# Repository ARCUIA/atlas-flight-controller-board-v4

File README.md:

# atlas-flight-controller-board-v4
Flight controller for 2026-2027 school year. KiCad v10. STM32F405RG-based board. Switching to SAM-M10Q GPS module.

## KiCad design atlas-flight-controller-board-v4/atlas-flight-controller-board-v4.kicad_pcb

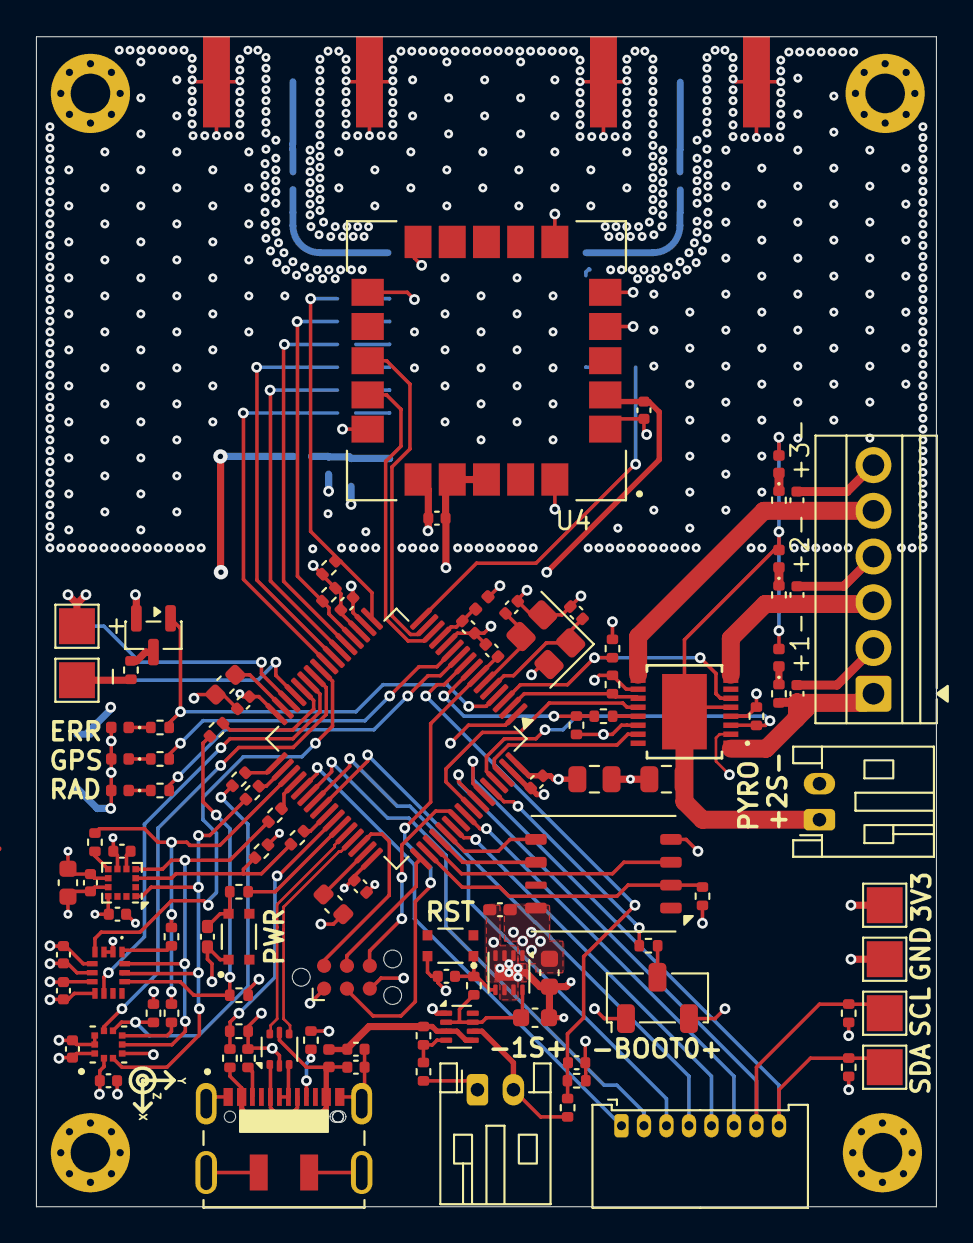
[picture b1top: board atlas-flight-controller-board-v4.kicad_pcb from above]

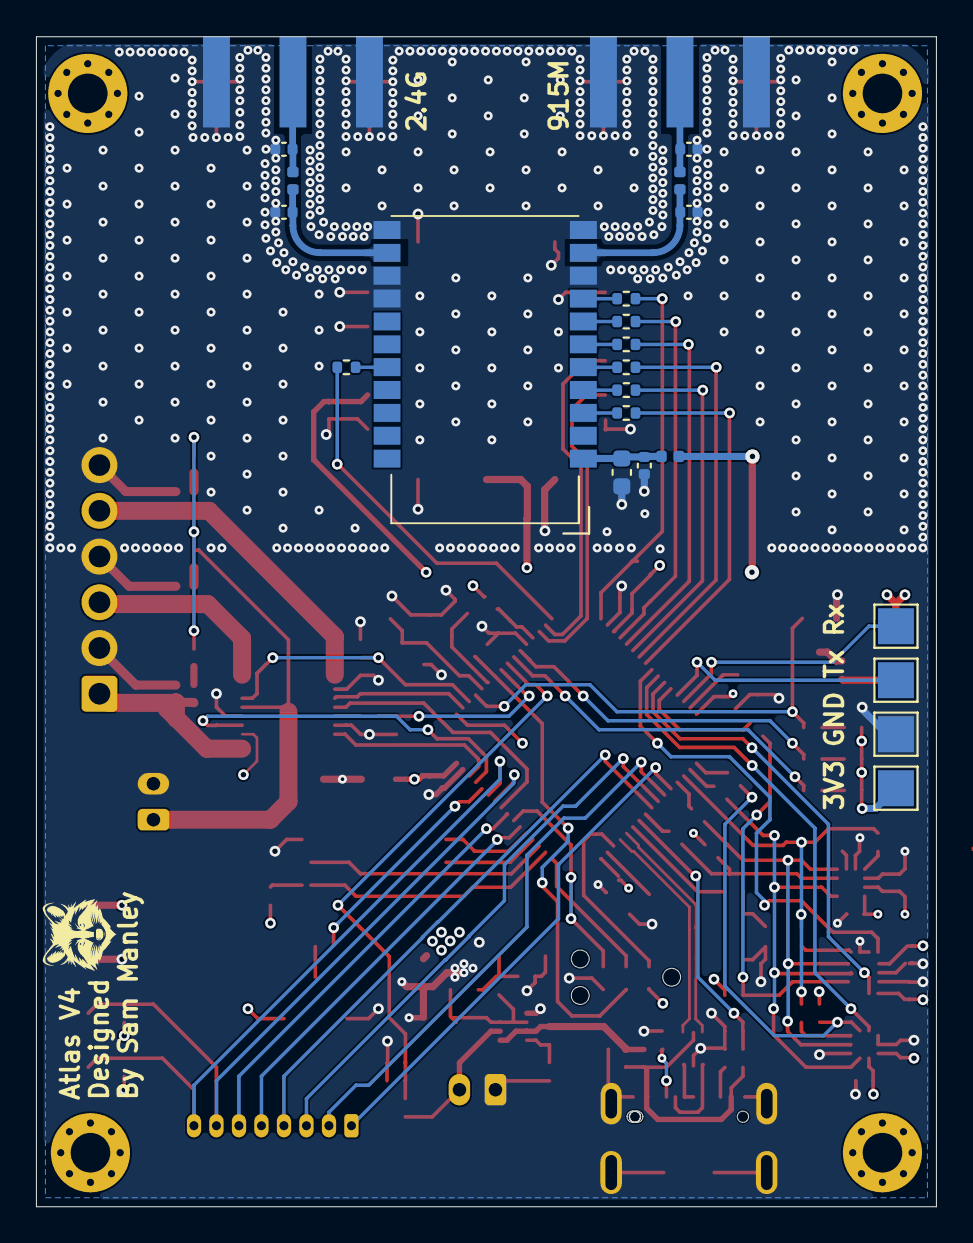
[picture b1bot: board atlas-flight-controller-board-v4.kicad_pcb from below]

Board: 4 copper layers, 50.0 x 65.0 mm, 134 parts (23 on the bottom side), 102 nets.

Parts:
A1: LPS22DFTR; XDCR_LPS22DFTR
C1: 4u7; C_0805_2012Metric
C3, C4, C5, C6, C7, C10, C17, C18, C19, C20, C22, C23, C25, C26, C32, C34, C35, C38, C39: 100n; C_0402_1005Metric
C11, C12: 10p; C_0402_1005Metric
C13, C14: 2u2; C_0603_1608Metric
C15, C16: 100n; C_0402_1005Metric_Pad0.74x0.62mm_HandSolder
C24, C33: 10u; C_0603_1608Metric
C27: 220n; C_0402_1005Metric
C28, C29, C30, C31: C_0402_1005Metric
C36, C37: 1u; C_0603_1608Metric
C40: 10u; C_0805_2012Metric
C41, C42, C43: 10n; C_0402_1005Metric
D1, D2, D3, D5, D6, D7: LED-Red; LED_0402_1005Metric
FB1, FB2, FB3: 120R @ 100 MHz; L_0402_1005Metric
H1, H2, H3, H4: MountingHole; MountingHole_2.2mm_M2_Pad_Via
IC1: LSM6DSV80XTR; LSM6DSV16BXTR
J1: DX07S016JA1R1500; JAE_DX07S016JA1R1500
J2: Conn_01x08; Molex_PicoBlade_53048-0810_1x08_P1.25mm_Horizontal
J3: SWD_TC2030-NL; Tag-Connect_TC2030-IDC-NL_2x03_P1.27mm_Vertical
J4, J5: Conn_Coaxial; SMA_Amphenol_132289_EdgeMount
J6: Batt Conn; JST_PH_S2B-PH-K_1x02_P2.00mm_Horizontal
J7: Conn_01x02; JST_PH_S2B-PH-K_1x02_P2.00mm_Horizontal
J8: Screw_Terminal_01x06; TerminalBlock_Xinya_XY308-2.54-6P_1x06_P2.54mm_Horizontal
L1, L2: L_0402_1005Metric
Q1: BSS138; SOT-23
R1, R10, R18, R21, R42, R43, R44, R45, R46, R47, R48: 10k; R_0402_1005Metric
R2, R20, R22: 33k; R_0402_1005Metric
R3: 82k; R_0402_1005Metric
R4, R5: 5k1; R_0402_1005Metric
R6, R7, R8, R9: 1k5; R_0402_1005Metric
R11, R12, R13, R14, R15, R16, R17: 470; R_0402_1005Metric
R19, R23: 100k; R_0402_1005Metric
R24, R25, R26, R27, R28, R29: 15k; R_0402_1005Metric
R30, R31: 330; R_0402_1005Metric
R34, R35, R36, R37, R38, R39, R40, R41: 33; R_0402_1005Metric
SW1: SW_SPDT; Nidec_Copal_CAS-120A
SW2: SW_Push; SW_USLPT2819DT2TR
SW3: HARD_RESET; SW_USLPT2819DT2TR
TP1, TP2, TP3, TP4, TP5, TP6, TP7, TP8, TP9, TP10: TestPoint_Square; TestPoint_Pad_2.0x2.0mm
U1: USBLC6; SOT-666
U2: STM32F405RGTx; LQFP-64_10x10mm_P0.5mm
U3: LGA-8_8x6.2mm_P1.27mm
U4: SAM-M10Q-00B; XCVR_SAM-M10Q-00B
U6: LIS2MDL; LGA-12_2x2mm_P0.5mm
U7: Value; Wio-LR2021_V1
U8: TPS7A2133PQWDSGRQ1; Texas_DSG0008A_WSON-8-1EP_2x2mm_P0.5mm_EP0.9x1.6mm
U9: TPS2116DRL; SOT-583-8
U13: VNQ7140AJTR; SOIC_0AJTR_STM
Y1: 16 MHz; Crystal_SMD_3225-4Pin_3.2x2.5mm

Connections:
+3.3VA: C7.1, FB1.1, U2.13 (VDDA)
+3V3: A1.1 (VDD_IO), A1.10 (VDD), C1.1, C3.1, C4.1, C5.1, C6.1, C15.1, C17.1, C18.1, C19.1, C20.2, C22.1, C23.1, C24.2, C25.2, C26.2, C36.1, D1.2 (A), D2.2 (A), D3.2 (A), FB1.2, FB2.2, IC1.5 (VDDIO), IC1.8 (VDD), J3.1 (VCC), R18.1, R42.1, R43.1, R44.1, R45.1, R46.1, R47.1, R48.1, SW1.3 (C), TP1.1 (1_1), TP5.1 (1_1), TP7.1 (1_1), U2.1 (VBAT), U2.19 (VDD), U2.32 (VDD), U2.48 (VDD), U2.64 (VDD), U3.8 (VDD), U4.2 (V_IO), U4.17 (VCC), U4.18 (~RESET), U6.9 (VDD), U6.10 (VDD_IO), U8.1 (OUT), U13.2 (SEN)
/power/MUX OUT: C37.1, R21.2, U8.8 (IN), U9.2 (VOUT), U9.7 (VOUT)
/power/VBATT+: J6.2, R22.1, U9.6 (VIN2)
/radio/2G4_RF_ANT: C28.1, J4.1 (In), L1.1
/radio/2G4_RF_MOD: C29.1, L1.2, U7.13 (2.4G_RF)
/radio/915_RF_ANT: C31.1, J5.1 (In), L2.1
/radio/915_RF_MOD: C30.1, L2.2, U7.10 (Sub-G_RF)
/stm32/BOOT0: R1.1, U2.60 (BOOT0)
/stm32/HSE_IN: C11.1, U2.5 (PH0), Y1.1
/stm32/HSE_OUT: C12.1, U2.6 (PH1), Y1.3
/stm32/SW_BOOT0: R1.2, SW1.2 (B)
/stm32/USB_DP+: J1.6 (D+), J1.7 (D+), U1.3 (I/O2), U1.4 (I/O2), U2.45 (PA12)
/stm32/USB_DP-: J1.5 (D-), J1.8 (D-), U1.1 (I/O1), U1.6 (I/O1), U2.44 (PA11)
/stm32/VBUS_SENSE: R2.1, R3.2, U2.42 (PA9)
BARO_INT: A1.7 (INT_DRDY), U2.26 (PB0)
BATT_SENSE: C38.1, R22.2, R23.1, U2.9 (PC1)
BUSY_LORA: R11.2, R18.2, U2.17 (PA3)
CAMERA_POWER_SWITCH: J2.6, U2.56 (PB4)
CS_BARO: A1.6 (CS), R39.1, R44.2
CS_FLASH: R45.2, U2.50 (PA15), U3.2 (CS)
CS_IMU: IC1.12 (CS), R40.1, R43.2
CS_LORA: R12.2, R46.2, U2.20 (PA4)
CS_MAG: R41.1, R42.2, U6.3 (CS)
ERROR_LED: Q1.1 (G), R8.2, U2.4 (PC15)
EXT_RX: TP10.1 (1_1), U2.30 (PB11)
EXT_SCL: J2.7, R47.2, TP3.1 (1_1), U2.58 (PB6)
EXT_SDA: J2.8, R48.2, TP4.1 (1_1), U2.59 (PB7)
EXT_TX: TP9.1 (1_1), U2.29 (PB10)
GND: A1.3 (RES), A1.8 (GND_IO), A1.9 (GND), C1.2, C3.2, C4.2, C5.2, C6.2, C7.2, C10.2, C11.2, C12.2, C13.2, C14.2, C15.2, C16.1, C17.2, C18.2, C19.2, C20.1, C22.2, C23.2, C24.1, C25.1, C26.1, C27.1, C28.2, C29.2, C30.2, C31.2, C32.2, C33.2, C34.2, C35.2, C36.2, C37.2, C38.2, C39.1, C40.2, C41.2, C42.2, C43.2, IC1.2 (SDX), IC1.3 (SCX), IC1.6 (GND_1), IC1.7 (GND_2), J1.1 (GND), J1.12 (GND), J1.S1 (SHIELD), J1.S2 (SHIELD), J1.S3 (SHIELD), J1.S4 (SHIELD), J1.S5 (SHIELD), J1.S6 (SHIELD), J3.5 (GND), J4.2 (Ext), J5.2 (Ext), J6.1, J7.2, J8.2, J8.4, J8.6, Q1.2 (S), R3.1, R4.1, R5.1, R20.2, R23.2, R27.2, R28.2, R29.2, R31.2, SW1.1 (A), SW2.1, SW3.2, TP2.1 (1_1), TP8.1 (1_1), U1.2 (GND), U2.12 (VSSA), U2.18 (VSS), U2.63 (VSS), U3.4 (GND), U4.1 (GND), U4.4 (GND), U4.5 (GND), U4.6 (GND), U4.10 (GND), U4.11 (GND), U4.15 (GND), U4.16 (GND), U4.20 (GND), U6.6 (GND), U6.8 (GND), U7.9 (GND), U7.11 (GND), U7.12 (GND), U7.14 (GND), U7.15 (GND), U8.2, U8.3, U8.4 (GND), U8.6, U8.7, U8.9 (PAD), U9.1 (GND), U13.4 (GND), U13.10 (SEL2), U13.14 (INPUT3), Y1.2, Y1.4
GPS_LED: R6.2, U2.10 (PC2)
IMU_INT1: IC1.4 (INT1), U2.25 (PC5)
IMU_INT2: IC1.9 (INT2), U2.27 (PB1)
IRQ_LORA: R14.1, U2.16 (PA2)
LORA_LED: R7.2, U2.11 (PC3)
MISO_FLASH: U2.52 (PC11), U3.6 (MISO)
MISO_LORA: R16.2, U2.22 (PA6)
MISO_MEMS: R34.2, R35.2, R36.2, U2.35 (PB14)
MOSI_FLASH: U2.53 (PC12), U3.5 (MOSI)
MOSI_LORA: R15.2, U2.23 (PA7)
MOSI_MEMS: A1.4 (SDA/SDI/SDO), IC1.14 (SDA), R38.1, U6.4 (SDA/SDI/SDO)
MOTOR_POWER_SWITCH: J2.5, U2.54 (PD2)
NRST: C10.1, J3.3 (~RESET), U2.7 (NRST)
unnamed: A1.5 (SDO/SA0), R36.1
unnamed: C16.2, R10.2, SW2.2
unnamed: D1.1 (K), R6.1
unnamed: D2.1 (K), R7.1
unnamed: D3.1 (K), R8.1
unnamed: D5.1 (K), R24.1
unnamed: D6.1 (K), R25.1
unnamed: D7.1 (K), R26.1
unnamed: IC1.1 (SDO/SA0), R35.1
unnamed: J1.3 (CC1), R4.2
unnamed: J1.9 (CC2), R5.2
unnamed: C43.1, J8.1, R26.2, U13.1 (OUTPUT0)
unnamed: C42.1, J8.3, R25.2, U13.8 (OUTPUT1)
unnamed: C41.1, J8.5, R24.2, U13.9 (OUTPUT2)
unnamed: Q1.3 (D), R9.2
unnamed: R9.1, TP6.1 (1_1)
unnamed: R41.2, U2.41 (PA8)
unnamed: R40.2, U2.28 (PB2)
unnamed: R39.2, U2.33 (PB12)
unnamed: R37.2, U2.34 (PB13)
unnamed: R38.2, U2.36 (PB15)
unnamed: C13.1, U2.31 (VCAP_1)
unnamed: C14.1, U2.47 (VCAP_2)
unnamed: C27.2, U6.5 (C1)
unnamed: R34.1, U6.7 (INT/DRDY/SDO)
unnamed: R11.1, U7.8 (BUSY)
unnamed: R14.2, U7.18 (DIO9)
unnamed: R16.1, U7.4 (MISO)
unnamed: R15.1, U7.5 (MOSI)
unnamed: R12.1, U7.7 (NSS)
unnamed: R17.1, U7.3 (RESET)
unnamed: R13.1, U7.6 (SCK)
unnamed: C32.1, C33.1, FB2.1, U7.1 (VCC_IN)
unnamed: C39.2, R21.1, SW3.1, U8.5 (EN)
unnamed: C35.1, FB3.2, R19.1, U9.3 (VIN1), U9.5 (MODE)
unnamed: R19.2, R20.1, U9.4 (PR1)
unnamed: R30.1, U13.13 (MULTISENSE)
PWM_MOTOR_1: J2.1, U2.37 (PC6)
PWM_MOTOR_2: J2.2, U2.38 (PC7)
PWM_MOTOR_3: J2.3, U2.39 (PC8)
PWM_MOTOR_4: J2.4, U2.40 (PC9)
PYRO_1: R29.1, U2.61 (PB8), U13.3 (INPUT0)
PYRO_2: R28.1, U2.3 (PC14), U13.6 (INPUT1)
PYRO_3: R27.1, U2.2 (PC13), U13.11 (INPUT2)
PYRO_BATT: C40.1, D5.2 (A), D6.2 (A), D7.2 (A), J7.1, U13.5 (FAULTRS_T), U13.17 (VCC)
PYRO_MULTISENSE: R30.2, R31.1, U2.8 (PC0)
PYRO_SEL0: U2.57 (PB5), U13.12 (SEL0)
PYRO_SEL1: U2.62 (PB9), U13.15 (SEL1)
RST_LORA: R17.2, U2.24 (PC4)
SCK_FLASH: U2.51 (PC10), U3.3 (CLK)
SCK_LORA: R13.2, U2.21 (PA5)
SCK_MEMS: A1.2 (SCL/SPC), IC1.13 (SCL), R37.1, U6.1 (SCL/SPC)
STANDBY_TOGGLE: R10.1, U2.43 (PA10)
SWCLK: J3.4 (SWCLK), U2.49 (PA14)
SWDIO: J3.2 (SWDIO), U2.46 (PA13)
SWO: J3.6 (SWO), U2.55 (PB3)
UART_GPS_TX_MCU_RX: U2.15 (PA1), U4.13 (TXD)
UART_MCU_TX_GPS_RX: U2.14 (PA0), U4.14 (RXD)
VBUS: C34.1, FB3.1, J1.2 (VBUS), J1.11 (VBUS), R2.2, U1.5 (VBUS)
